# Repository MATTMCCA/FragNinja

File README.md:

# Frag-Ninja

Wii Nunchuk 2 USB HID device, modchip repo. 

This board prototype should fit **in** a wii Nunchuk controller, ~~*I did not double check the clearance*~~.  

The Goal is to use the Nunchuk controller as a USB HID keyboard *OR* USB HID Gamepad, after connecting the *mod-chip*. 
The nunchuk also has 3 axis motion control. *(This, I'm not interested in)*.

[Digikey Cart with Reference Designators](https://www.digikey.com/short/zw3pv2)

<p>

[*I'm not making kits, its too much work*](https://memegenerator.net/img/instances/65580880/not-sure-if-its-too-much-work-or-im-just-too-lazy.jpg)

---

### Notes
~~Using the the controllers attached cable is an option~~, but I opted for a new, longer, shielded, USB cable.

USB cable assembly parts purchased from [ZapCables.com](https://zapcables.com/diy-usb-cable-kit/)

- Cable length: ~~3ft~~, 6'
- USB Type-A connector (Gold Plated)
- Cord color: ~~'Acid Purple'~~, 'Viper'
- Double Sleeving: ~~Techflex, Ogre~~, None
- HeatShrink: ~~Purple~~, Black

Cable Build Guide: https://zapcables.com/content/zap-diy-usb-cable-kit-guide-v1.pdf

- **I think I linked the wrong LED in the BOM**.

---
### To Flash The Adafruit Bootloader

Solder Wires to **SWCLK & SWDIO**. Vref connects to pad **VCC** (this is 3.3vdc). Then supply 5vdc to the **5v** pad, and ground to the **GND** pad

I used this [Guide](https://learn.adafruit.com/how-to-program-samd-bootloaders/trinket-m0-wiring) & this [Guide](https://learn.adafruit.com/how-to-program-samd-bootloaders/programming-the-bootloader-with-atmel-studio) as a reference. Since Frag-Ninja is basically a clone of the *Trinket M0*, the procedure is exactly the same.

---

#### See Bill of Materials for board assembly part numbers.

- [Wii Nunchuck Controller](https://www.amazon.com/gp/product/B07RLBN9Z2)
- [Analog Thumb Stick Caps](https://www.amazon.com/gp/product/B07Q2B2VY4)
- [Skull Cap Covers](https://www.amazon.com/gp/product/B07GS95TD1)

### More Info
This 'mod-chip' is based on the *adafruit Trinket M0*, as a result I am able to use their boot-loader & arduino libs. This makes life just a tad bit easier (less code). 

*Big thanks to Adafriut for all of their hard work and great products.*

## Work in Progress

-  Boards have been ordered (9/13/2020)
   - BOARDS CAME! (9/26/2020)
---
-  Parts have been ordered (9/13/2020)
---
-  USB Cable kit has been ordered (9/13/2020)
   - *Cable Assembled, I should have got a 5' cable (9/17/2020)*
      - *was replaced with a 6' cable (9/23/2020)*
---	  
- **NEED TO ASSEMBLE THE PCB**
   - *PCB assembled (9/26/2020)*
---   
- **NEED TO BURN THE BOOTLOADER**
   - *Bootloader burned (9/26/2020)*
---   
- **NEED TO TEST THE HARDWARE**
   - *Tested and working (9/26/2020)*
---   
- **NEED TO FLASH CODE**
   - *Code tested & working (9/26/2020)*
---   
- **NEED TO HACK APART A WII Nunchuk**
   - *Gave a new white controller a fresh coat of lime green paint (9/24/2020)*
   - *Test fitted an **Xbox 360** after-market 'Analog Thumb Stick Cap' (9/24/2020)*.
   - *Frag-Ninja ModChip installed and working (9/26/2020)*
---
- **NEED TO FRAG!**

# WHY!?

Because I can't find a cheap joystick! I guess they aren't cool anymore or something.

# Copyright

Everything in this repo is released under Creative Commons Attribution-ShareAlike 2.5 Generic (CC BY-SA 2.5).

Comes as is, no warranty. I am also not responsible for any spontaneous time travel or combustion.

*Moved from my old repo*

### Borrowed works maintain original license.

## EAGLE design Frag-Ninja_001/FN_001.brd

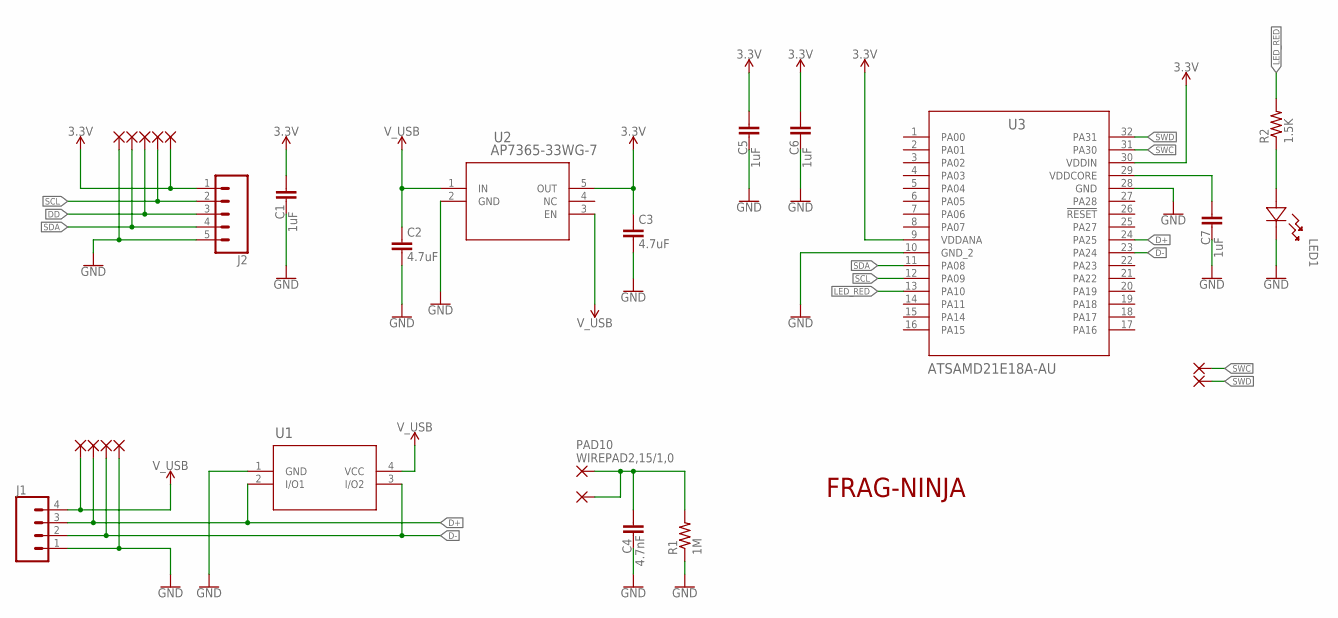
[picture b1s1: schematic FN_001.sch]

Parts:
C1, C5, C6, C7: 1uF; C0603K
C2, C3: 4.7uF; C0603K
C4: 4.7nF; C0603K
J1: CONN_04PTH; 1X04
J2: CONN_05; 1X05
LED1: SML-D12U1WT86; LED_SMLD12_ROM
PAD1, PAD2, PAD3, PAD4, PAD5, PAD6, PAD7, PAD8, PAD9, PAD12, PAD13: WIREPADSMD1,27-254; SMD1,27-2,54
PAD10: WIREPAD2,15/1,0; 2,15/1,0
PAD11: WIREPADSMD2,54-5,08; SMD2,54-5,08
R1: 1M; R0603
R2: 1.5K; R0603
U1: PRTR5V0U2X; SOT143B_NXP
U2: AP7365-33WG-7; SOT25_DIO
U3: ATSAMD21E18A-AU; TQFP32_MC_MCH

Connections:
3.3V: C1.1, C3.1, C5.1, C6.1, J2.1, PAD9.1, U2.5 (OUT), U3.9 (VDDANA), U3.30 (VDDIN)
D+: J1.3, PAD2.1, U1.2 (I/O1), U3.24 (PA25)
D-: J1.2, PAD3.1, U1.3 (I/O2), U3.23 (PA24)
DD: J2.3, PAD7.1
GND: C1.2, C2.2, C3.2, C4.2, C5.2, C6.2, C7.2, J1.1, J2.5, LED1.1, PAD4.1, PAD5.1, R1.1, U1.1 (GND), U2.2 (GND), U3.10 (GND_2), U3.28 (GND)
LED_RED: R2.2, U3.13 (PA10)
unnamed: LED1.2, R2.1
unnamed: C4.1, PAD10.1, PAD11.1, R1.2
unnamed: C7.1, U3.29 (VDDCORE)
SCL: J2.2, PAD8.1, U3.12 (PA09)
SDA: J2.4, PAD6.1, U3.11 (PA08)
SWC: PAD12.1, U3.31 (PA30)
SWD: PAD13.1, U3.32 (PA31)
V_USB: C2.1, J1.4, PAD1.1, U1.4 (VCC), U2.1 (IN), U2.3 (EN)

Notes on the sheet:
FRAG-NINJA

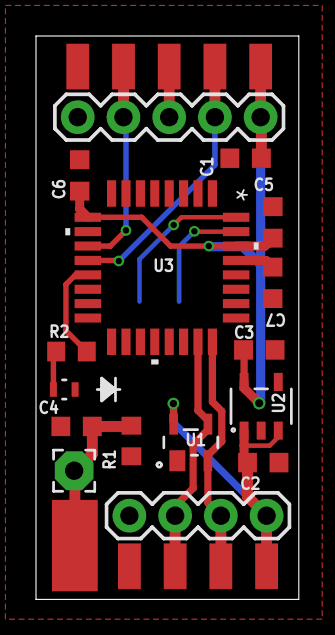
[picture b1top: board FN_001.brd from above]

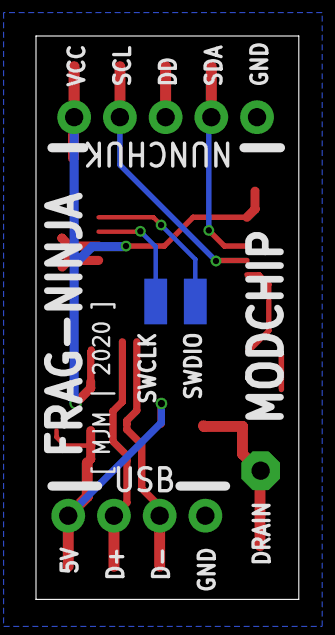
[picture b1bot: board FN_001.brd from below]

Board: 2 copper layers, 14.6 x 31.3 mm, 28 parts (2 on the bottom side), 14 nets.

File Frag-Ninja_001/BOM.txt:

Partlist

Exported from FN_001.sch at 9/13/2020 12:08 AM

EAGLE Version 9.5.0 Copyright (c) 1988-2019 Autodesk, Inc.

Assembly variant: 

Part     Value               Device              Package        Library             Sheet       Digikey Part#

C1       1uF                 C-EUC0603K          C0603K         rcl                 1           1276-1182-1-ND

C2       4.7uF               C-EUC0603K          C0603K         rcl                 1           445-14258-1-ND
C3       4.7uF               C-EUC0603K          C0603K         rcl                 1           445-14258-1-ND

C4       4.7nF               C-EUC0603K          C0603K         rcl                 1           399-1087-2-ND

C5       1uF                 C-EUC0603K          C0603K         rcl                 1           1276-1182-1-ND
C6       1uF                 C-EUC0603K          C0603K         rcl                 1           1276-1182-1-ND
C7       1uF                 C-EUC0603K          C0603K         rcl                 1           1276-1182-1-ND

LED1     RED                 SML-D12U1WT86       LED_SMLD12_ROM SML-D12U1WT86       1           SML-D12U1WT86CT-ND

R1       1M                  R-US_R0603          R0603          rcl                 1           A130452CT-ND

R2       1.5K                R-US_R0603          R0603          rcl                 1           A130092CT-ND

U1       PRTR5V0U2X,215      PRTR5V0U2X          SOT143B_NXP    PRTR5V0U2X          1           1727-3884-1-ND

U2       AP7365-33WG-7       AP7365-33WG-7       SOT25_DIO      AP7365-33WG-7       1           AP7365-33WG-7DICT-ND

U3       ATSAMD21E18A-AU     ATSAMD21E18A-AU     TQFP32_MC_MCH  ATSAMD21E18A-AU     1           ATSAMD21E18A-AU-ND

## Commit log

2021-08-27 init

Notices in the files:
parts and their libraries:
SparkFun-Connectors: Licensing: Creative Commons ShareAlike 4.0 International - https://creativecommons.org/licenses/by-sa/4.0
COPYRIGHT: Copyright (C) 2018 Accelerated Designs. All rights reserved
